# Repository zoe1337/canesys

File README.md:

# CANesys

Over CAN you said: let there be light (with 30% brightness).

And it was light (with 30% duty cycle).

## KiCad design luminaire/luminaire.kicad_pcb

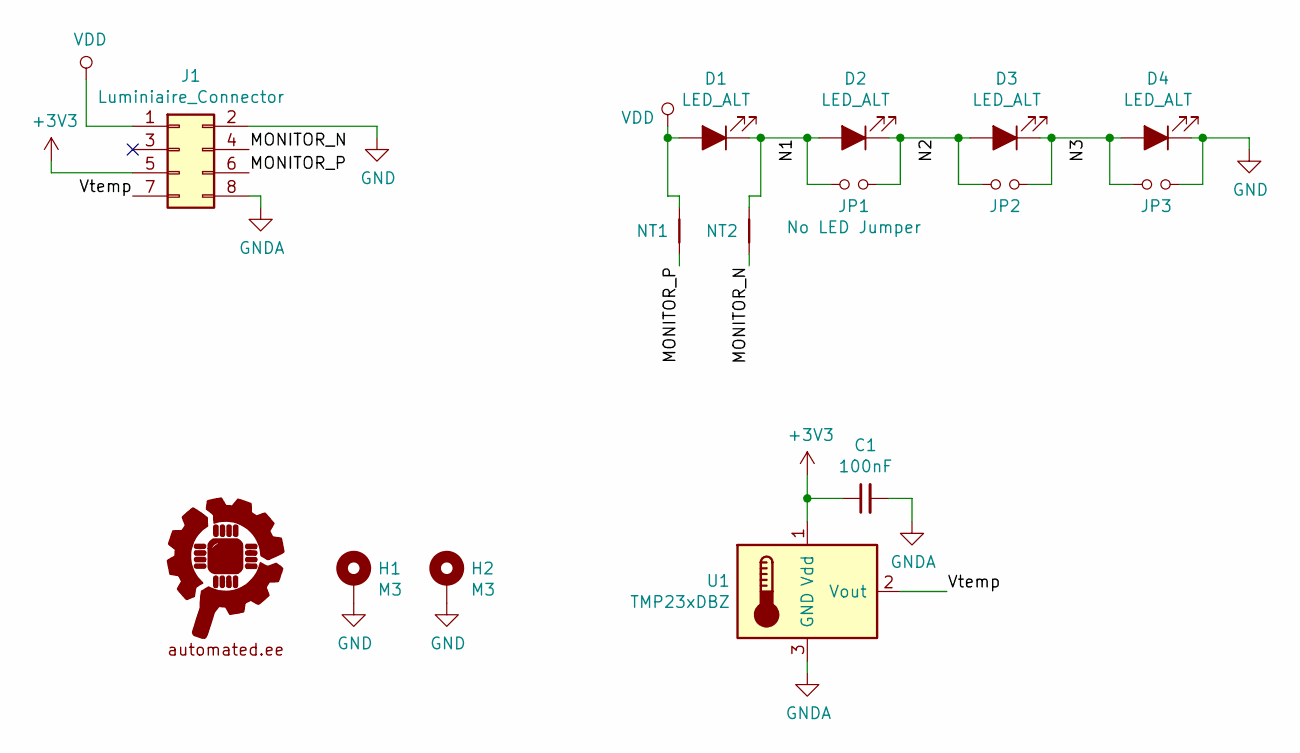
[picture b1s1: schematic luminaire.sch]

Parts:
C1: 100nF; C_0603_1608Metric
D1, D2, D3, D4: LED_ALT; LED_Osram_DURIS_S5_3x2.55x0.6mm
G1: Fully_Automated_Logo; falogo_small_copper
H1, H2: M3; MountingHole_3.2mm_M3_Pad_Via
J1: Luminiaire_Connector; PinHeader_2x04_P2.54mm_Vertical_SMD
JP1, JP2, JP3: No LED Jumper; SolderJumper-2_P1.3mm_Open_Pad1.0x1.5mm
NT1: MONITOR_P; NetTie-2_SMD_Pad0.5mm
NT2: NONITOR_N; NetTie-2_SMD_Pad0.5mm
U1: TMP23xDBZ; SOT-23

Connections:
+3V3: C1.1, J1.5, U1.1 (Vdd)
/MONITOR_N: J1.4, NT2.2
/MONITOR_P: J1.6, NT1.2
/N1: D1.1 (K), D2.2 (A), JP1.1, NT2.1
/N2: D2.1 (K), D3.2 (A), JP1.2, JP2.1
/N3: D3.1 (K), D4.2 (A), JP2.2, JP3.1
/Vtemp: J1.7, U1.2 (Vout)
GND: D4.1 (K), H1.1, H2.1, J1.2, JP3.2
GNDA: C1.2, J1.8, U1.3 (GND)
VDD: D1.2 (A), J1.1, NT1.1

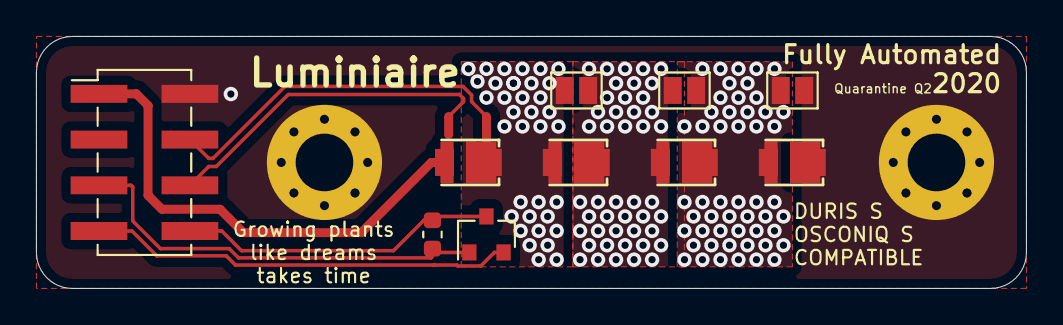
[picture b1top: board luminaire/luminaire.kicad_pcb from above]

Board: 2 copper layers, 55.0 x 14.0 mm, 15 parts (1 on the bottom side), 10 nets.

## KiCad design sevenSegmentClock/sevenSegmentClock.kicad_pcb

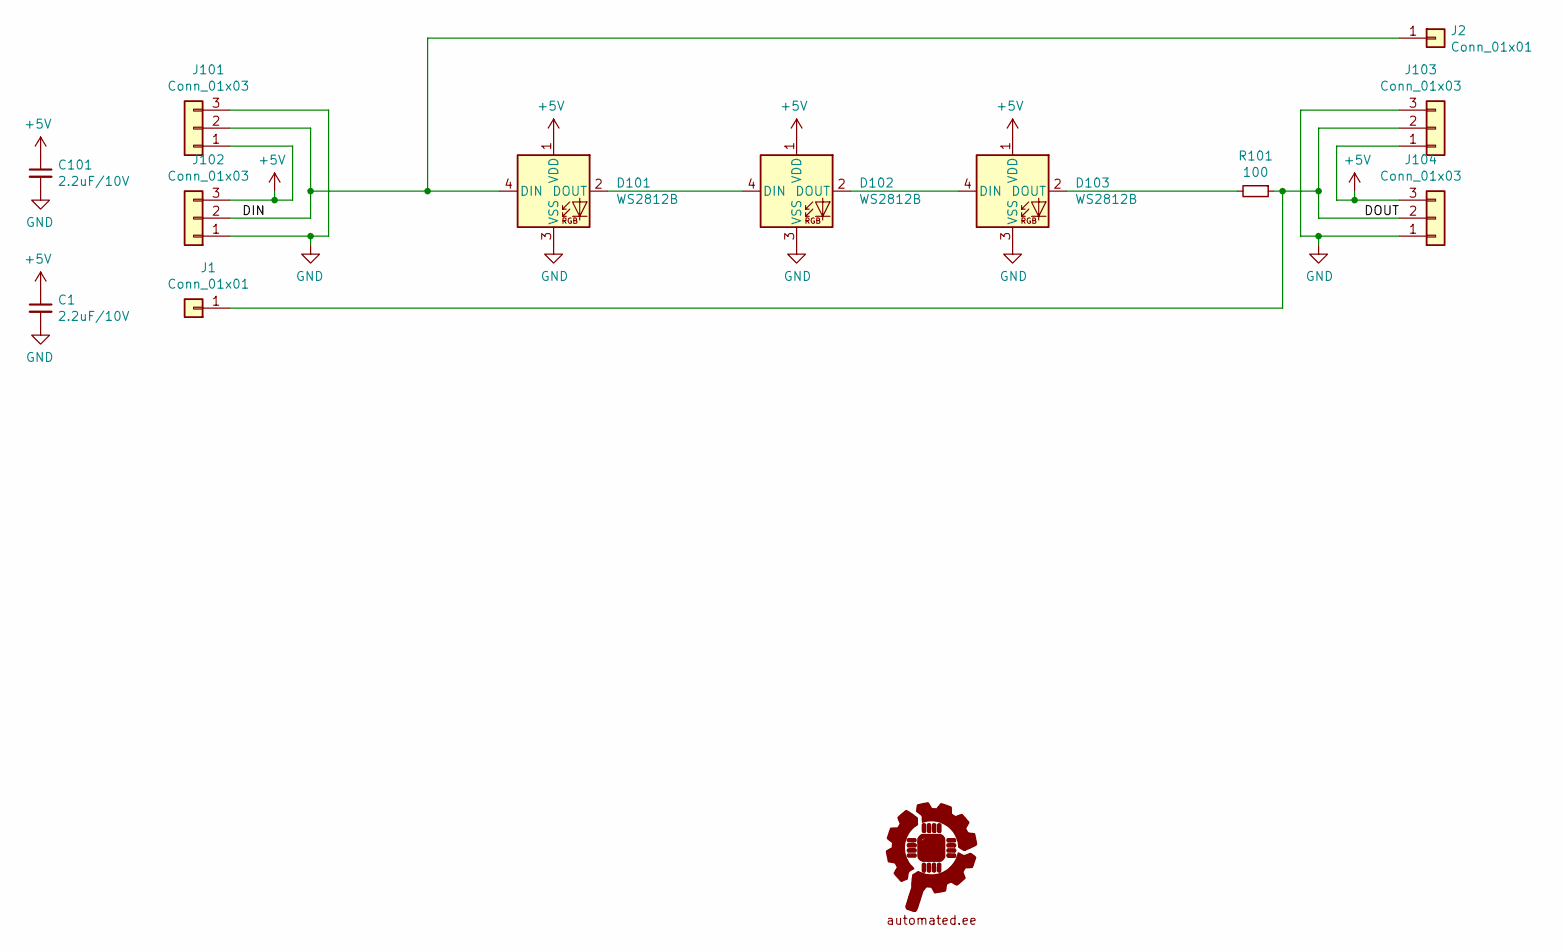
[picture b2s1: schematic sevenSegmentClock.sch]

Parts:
C1, C101: 2.2uF/10V; C_0603_1608Metric
D101, D102, D103: WS2812B; LED_SK6812MINI_PLCC4_3.5x3.5mm_P1.75mm
G101: Fully_Automated_Logo; fully_automated_logo_soldermask
J1, J2: Conn_01x01; TestPoint_THTPad_1.5x1.5mm_Drill0.7mm
J101, J102, J103, J104: Conn_01x03; PinHeader_1x03_P2.00mm_Vertical
R101: 100; R_0603_1608Metric

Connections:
+5V: C1.1, C101.1, D101.1 (VDD), D102.1 (VDD), D103.1 (VDD), J101.1, J102.3, J103.1, J104.3
/DIN: D101.4 (DIN), J2.1, J101.2, J102.2
/DOUT: J1.1, J103.2, J104.2, R101.1
GND: C1.2, C101.2, D101.3 (VSS), D102.3 (VSS), D103.3 (VSS), J101.3, J102.1, J103.3, J104.1
unnamed: D101.2 (DOUT), D102.4 (DIN)
unnamed: D102.2 (DOUT), D103.4 (DIN)
unnamed: D103.2 (DOUT), R101.2

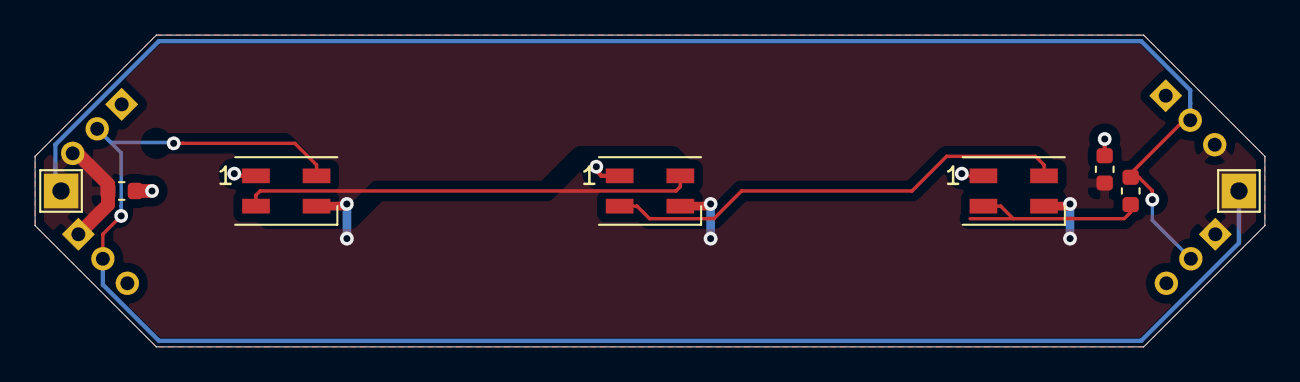
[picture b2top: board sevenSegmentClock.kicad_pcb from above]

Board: 2 copper layers, 71.0 x 18.0 mm, 13 parts (1 on the bottom side), 7 nets.

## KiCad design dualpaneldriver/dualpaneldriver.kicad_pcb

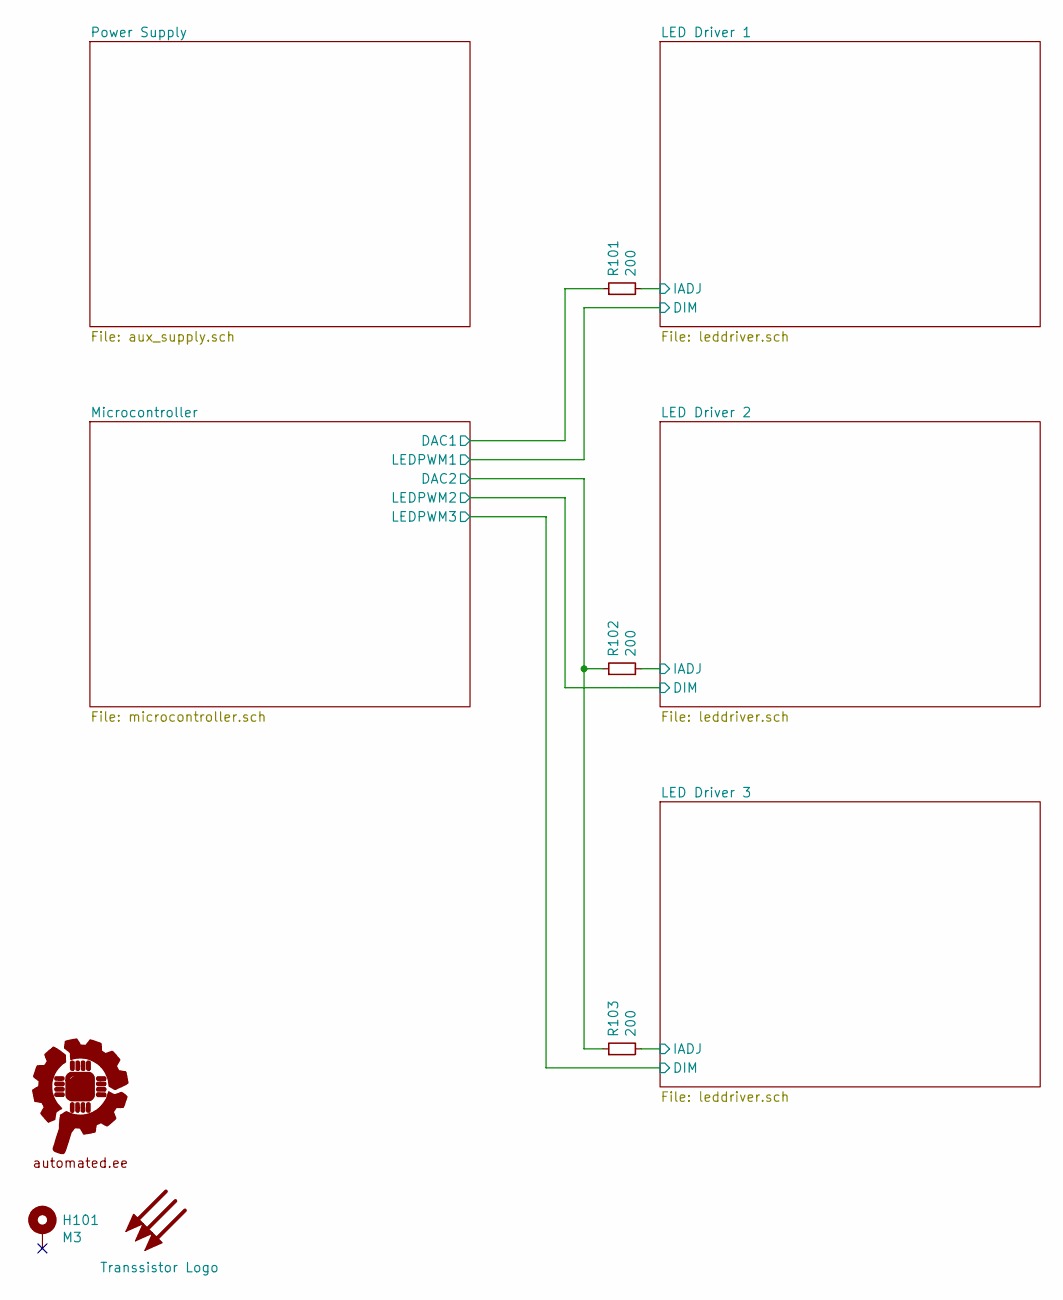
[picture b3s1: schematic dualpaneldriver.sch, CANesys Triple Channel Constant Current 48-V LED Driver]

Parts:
G101: Fully_Automated_Logo; falogo_small_copper
G102: Transsistor Logo; transistor_10x10mm
H101: M3; MountingHole_3.2mm_M3_ISO7380_Pad
R101, R102, R103: 200; R_0603_1608Metric

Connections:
/LED Driver 1/IADJ: R101.2; also elsewhere on the board
/LED Driver 2/IADJ: R102.2; also elsewhere on the board
/LED Driver 3/IADJ: R103.2; also elsewhere on the board
/Microcontroller/DAC1: R101.1; also elsewhere on the board
/Microcontroller/DAC2: R102.1, R103.1; also elsewhere on the board

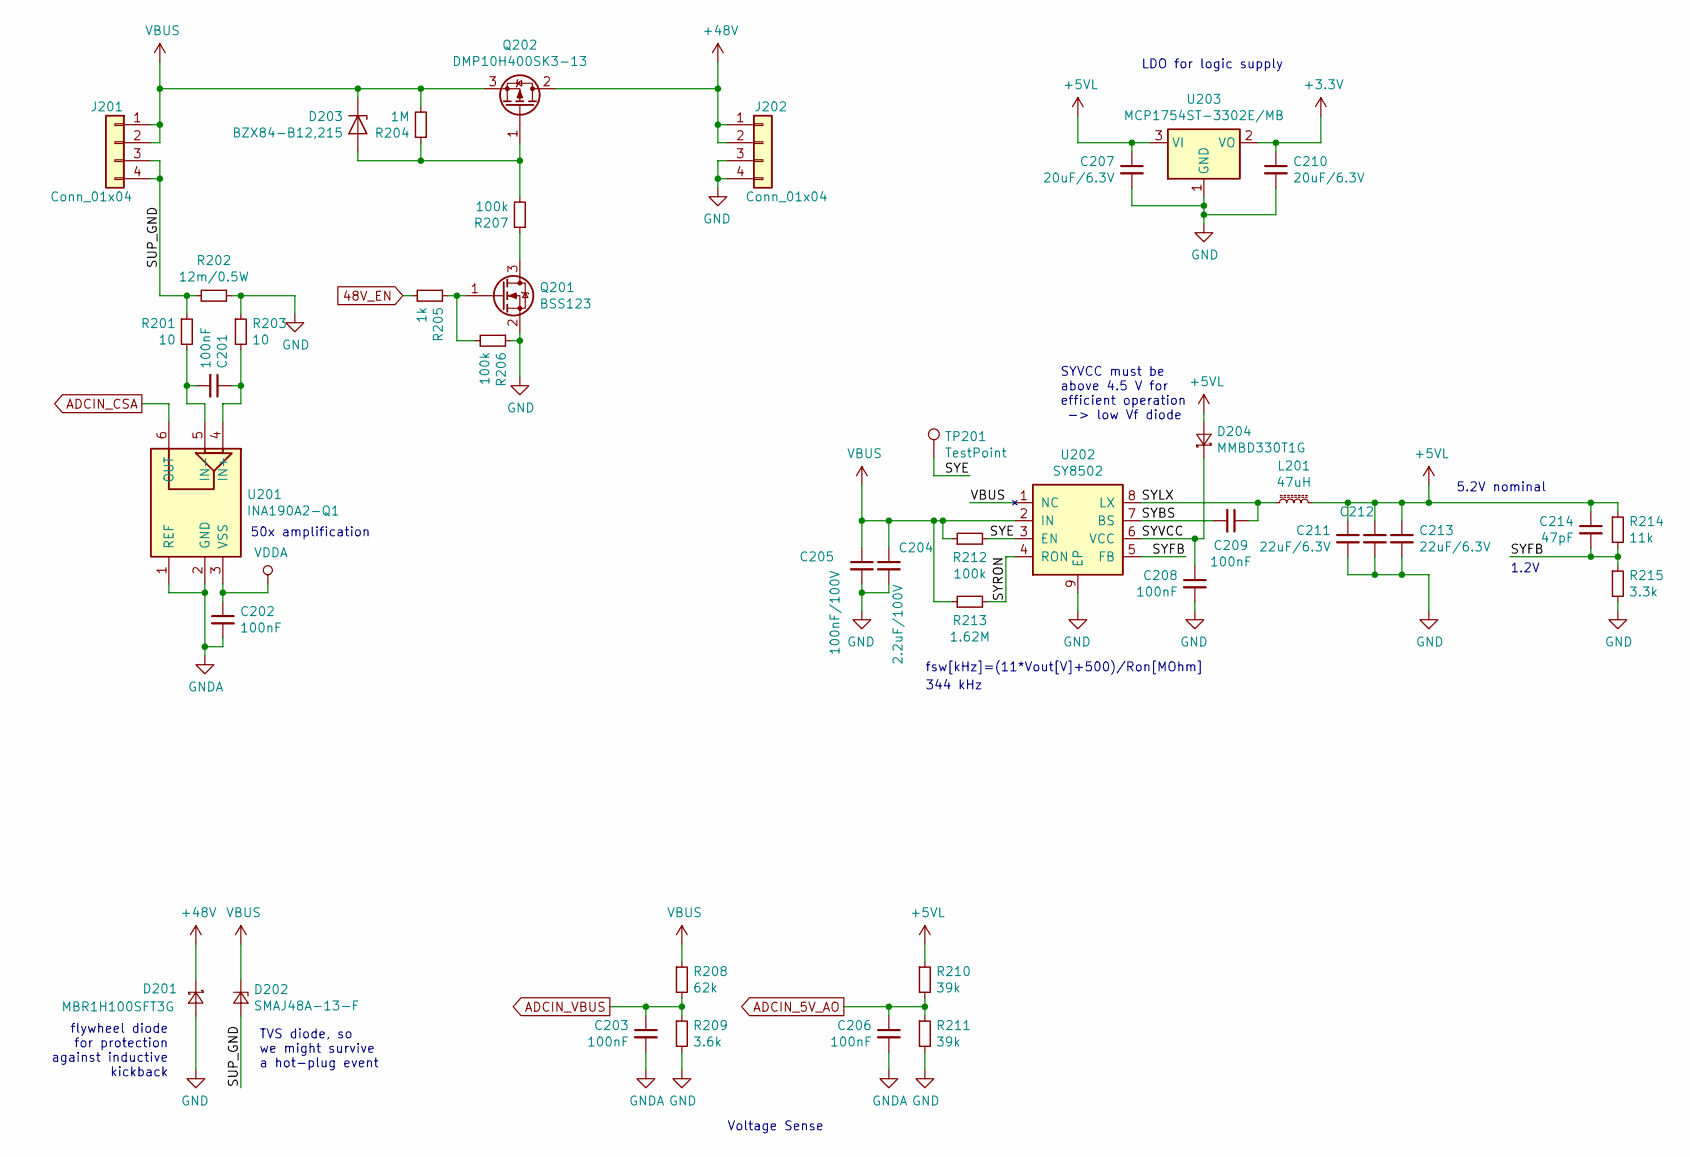
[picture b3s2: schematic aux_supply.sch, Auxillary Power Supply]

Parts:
C201, C202, C203, C206, C208: 100nF; C_0603_1608Metric
C204: 100nF/100V; C_0603_1608Metric
C205: 2.2uF/100V; C_1210_3225Metric
C207, C210: 20uF/6.3V; C_0805_2012Metric
C209: 100nF; C_0402_1005Metric
C211, C212, C213: 22uF/6.3V; C_0603_1608Metric
C214: 47pF; C_0603_1608Metric
D201: MBR1H100SFT3G; D_SOD-123F
D202: SMAJ48A-13-F; D_SMA
D203: BZX84-B12,215; D_SOT-23_ANK
D204: MMBD330T1G; D_SOT-23_ANK
J201, J202: Conn_01x04; PinHeader_1x04_P2.54mm_Horizontal
L201: 47uH; L_Bourns_SRN6045TA
Q201: BSS123; SOT-23
Q202: DMP10H400SK3-13; TO-252-2
R201, R203: 10; R_0603_1608Metric
R202: 12m/0.5W; R_2512_6332Metric
R204: 1M; R_0603_1608Metric
R205: 1k; R_0603_1608Metric
R206, R207, R212: 100k; R_0603_1608Metric
R208: 62k; R_0603_1608Metric
R209: 3.6k; R_0603_1608Metric
R210, R211: 39k; R_0603_1608Metric
R213: 1.62M; R_0603_1608Metric
R214: 11k; R_0603_1608Metric
R215: 3.3k; R_0603_1608Metric
TP201: TestPoint; TestPoint_Pad_1.0x1.0mm
U201: INA190A2-Q1; SOT-363_SC-70-6
U202: SY8502; SO8E_Silergy_4x5mm_EP3.4x2.55mm
U203: MCP1754ST-3302E/MB; SOT-89-3

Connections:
48V_EN: R205.2; also elsewhere on the board
+3V3: C210.1, U203.2 (VO); also elsewhere on the board
+5VL: C207.1, C211.1, C212.1, C213.1, C214.1, D204.2 (A), L201.2, R210.1, R214.1, U203.3 (VI); also elsewhere on the board
+48V: D201.1 (K), J202.1, J202.2, Q202.2 (D); also elsewhere on the board
/Power Supply/SUP_GND: D202.2 (A), J201.3, J201.4, R201.1, R202.2
/Power Supply/SYBS: C209.2, U202.7 (BS)
/Power Supply/SYE: R212.2, TP201.1, U202.3 (EN)
/Power Supply/SYFB: C214.2, R214.2, R215.1, U202.5 (FB)
/Power Supply/SYLX: C209.1, L201.1, U202.8 (LX)
/Power Supply/SYRON: R213.2, U202.4 (RON)
/Power Supply/SYVCC: C208.1, D204.1 (K), U202.6 (VCC)
ADCIN_5V_AO: C206.1, R210.2, R211.1; also elsewhere on the board
ADCIN_CSA: U201.6 (OUT); also elsewhere on the board
ADCIN_VBUS: C203.1, R208.2, R209.1; also elsewhere on the board
GND: C204.2, C205.2, C207.2, C208.2, C210.2, C211.2, C212.2, C213.2, D201.2 (A), J202.3, J202.4, Q201.2 (S), R202.1, R203.1, R206.1, R209.2, R211.2, R215.2, U202.9 (EP), U203.1 (GND); also elsewhere on the board
GNDA: C202.2, C203.2, C206.2, U201.1 (REF), U201.2 (GND); also elsewhere on the board
unnamed: C201.1, R203.2, U201.4 (IN+)
unnamed: C201.2, R201.2, U201.5 (IN-)
unnamed: D203.2 (A), Q202.1 (G), R204.1, R207.2
unnamed: Q201.1 (G), R205.1, R206.2
unnamed: Q201.3 (D), R207.1
VBUS: C204.1, C205.1, D202.1 (K), D203.1 (K), J201.1, J201.2, Q202.3 (S), R204.2, R208.1, R212.1, R213.1, U202.1 (NC), U202.2 (IN)
VDDA: C202.1, U201.3 (VSS); also elsewhere on the board

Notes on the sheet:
50x amplification
TVS diode, so we might survive a hot-plug event
5.2V nominal
344 kHz
fsw[kHz]=(11*Vout[V]+500)/Ron[MOhm]
1.2V
SYVCC must be above 4.5 V for efficient operation -> low Vf diode
flywheel diode for protection against inductive kickback
LDO for logic supply
Voltage Sense

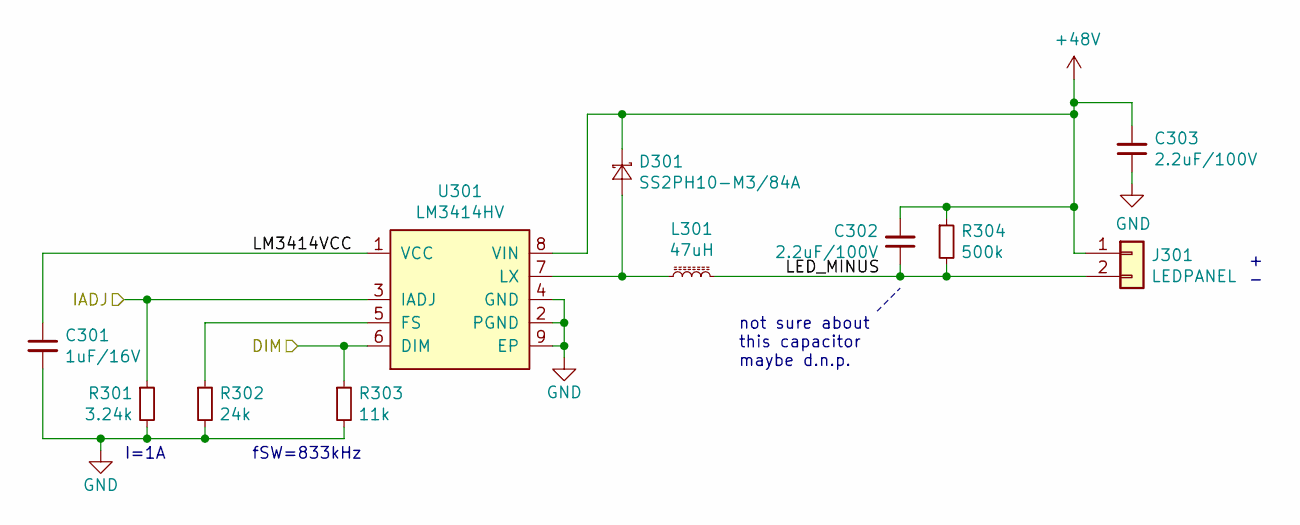
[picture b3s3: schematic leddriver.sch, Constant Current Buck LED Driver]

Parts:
C301: 1uF/16V; C_0603_1608Metric
C302, C303: 2.2uF/100V; C_1206_3216Metric
D301: SS2PH10-M3/84A; D_SMP_DO-220AA
J301: LEDPANEL; PinHeader_1x02_P2.54mm_Vertical
L301: 47uH; L_Bourns_SRN6045TA
R301: 3.24k; R_0603_1608Metric
R302: 24k; R_0603_1608Metric
R303: 11k; R_0603_1608Metric
R304: 500k; R_0603_1608Metric
U301: LM3414HV; SOIC-8-1EP_3.9x4.9mm_P1.27mm_EP2.29x3mm

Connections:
+48V: C302.2, C303.2, D301.1 (K), J301.1, R304.1, U301.8 (VIN); also elsewhere on the board
/LED Driver 1/DIM: R303.1, U301.6 (DIM); also elsewhere on the board
/LED Driver 1/IADJ: R301.1, U301.3 (IADJ); also elsewhere on the board
/LED Driver 1/LED_MINUS: C302.1, J301.2, L301.2, R304.2
/LED Driver 1/LM3414VCC: C301.1, U301.1 (VCC)
GND: C301.2, C303.1, R301.2, R302.2, R303.2, U301.2 (PGND), U301.4 (GND), U301.9 (EP); also elsewhere on the board
unnamed: D301.2 (A), L301.1, U301.7 (LX)
unnamed: R302.1, U301.5 (FS)

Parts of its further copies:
C501, C601: 1uF/16V; C_0603_1608Metric
C502, C503, C602, C603: 2.2uF/100V; C_1206_3216Metric
D501, D601: SS2PH10-M3/84A; D_SMP_DO-220AA
J501, J601: LEDPANEL; PinHeader_1x02_P2.54mm_Vertical
L501, L601: 47uH; L_Bourns_SRN6045TA
R501, R601: 3.24k; R_0603_1608Metric
R502, R602: 24k; R_0603_1608Metric
R503, R603: 11k; R_0603_1608Metric
R504, R604: 500k; R_0603_1608Metric
U501, U601: LM3414HV; SOIC-8-1EP_3.9x4.9mm_P1.27mm_EP2.29x3mm

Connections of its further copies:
+48V: C502.2, C503.2, C602.2, C603.2, D501.1 (K), D601.1 (K), J501.1, J601.1, R504.1, R604.1, U501.8 (VIN), U601.8 (VIN); also elsewhere on the board
/LED Driver 2/DIM: R503.1, U501.6 (DIM); also elsewhere on the board
/LED Driver 2/IADJ: R501.1, U501.3 (IADJ); also elsewhere on the board
/LED Driver 2/LED_MINUS: C502.1, J501.2, L501.2, R504.2
/LED Driver 2/LM3414VCC: C501.1, U501.1 (VCC)
/LED Driver 3/DIM: R603.1, U601.6 (DIM); also elsewhere on the board
/LED Driver 3/IADJ: R601.1, U601.3 (IADJ); also elsewhere on the board
/LED Driver 3/LED_MINUS: C602.1, J601.2, L601.2, R604.2
/LED Driver 3/LM3414VCC: C601.1, U601.1 (VCC)
GND: C501.2, C503.1, C601.2, C603.1, R501.2, R502.2, R503.2, R601.2, R602.2, R603.2, U501.2 (PGND), U501.4 (GND), U501.9 (EP), U601.2 (PGND), U601.4 (GND), U601.9 (EP); also elsewhere on the board
unnamed: D501.2 (A), L501.1, U501.7 (LX)
unnamed: D601.2 (A), L601.1, U601.7 (LX)
unnamed: R502.1, U501.5 (FS)
unnamed: R602.1, U601.5 (FS)

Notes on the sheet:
fSW=833kHz
I=1A
not sure about this capacitor maybe d.n.p.
+ -

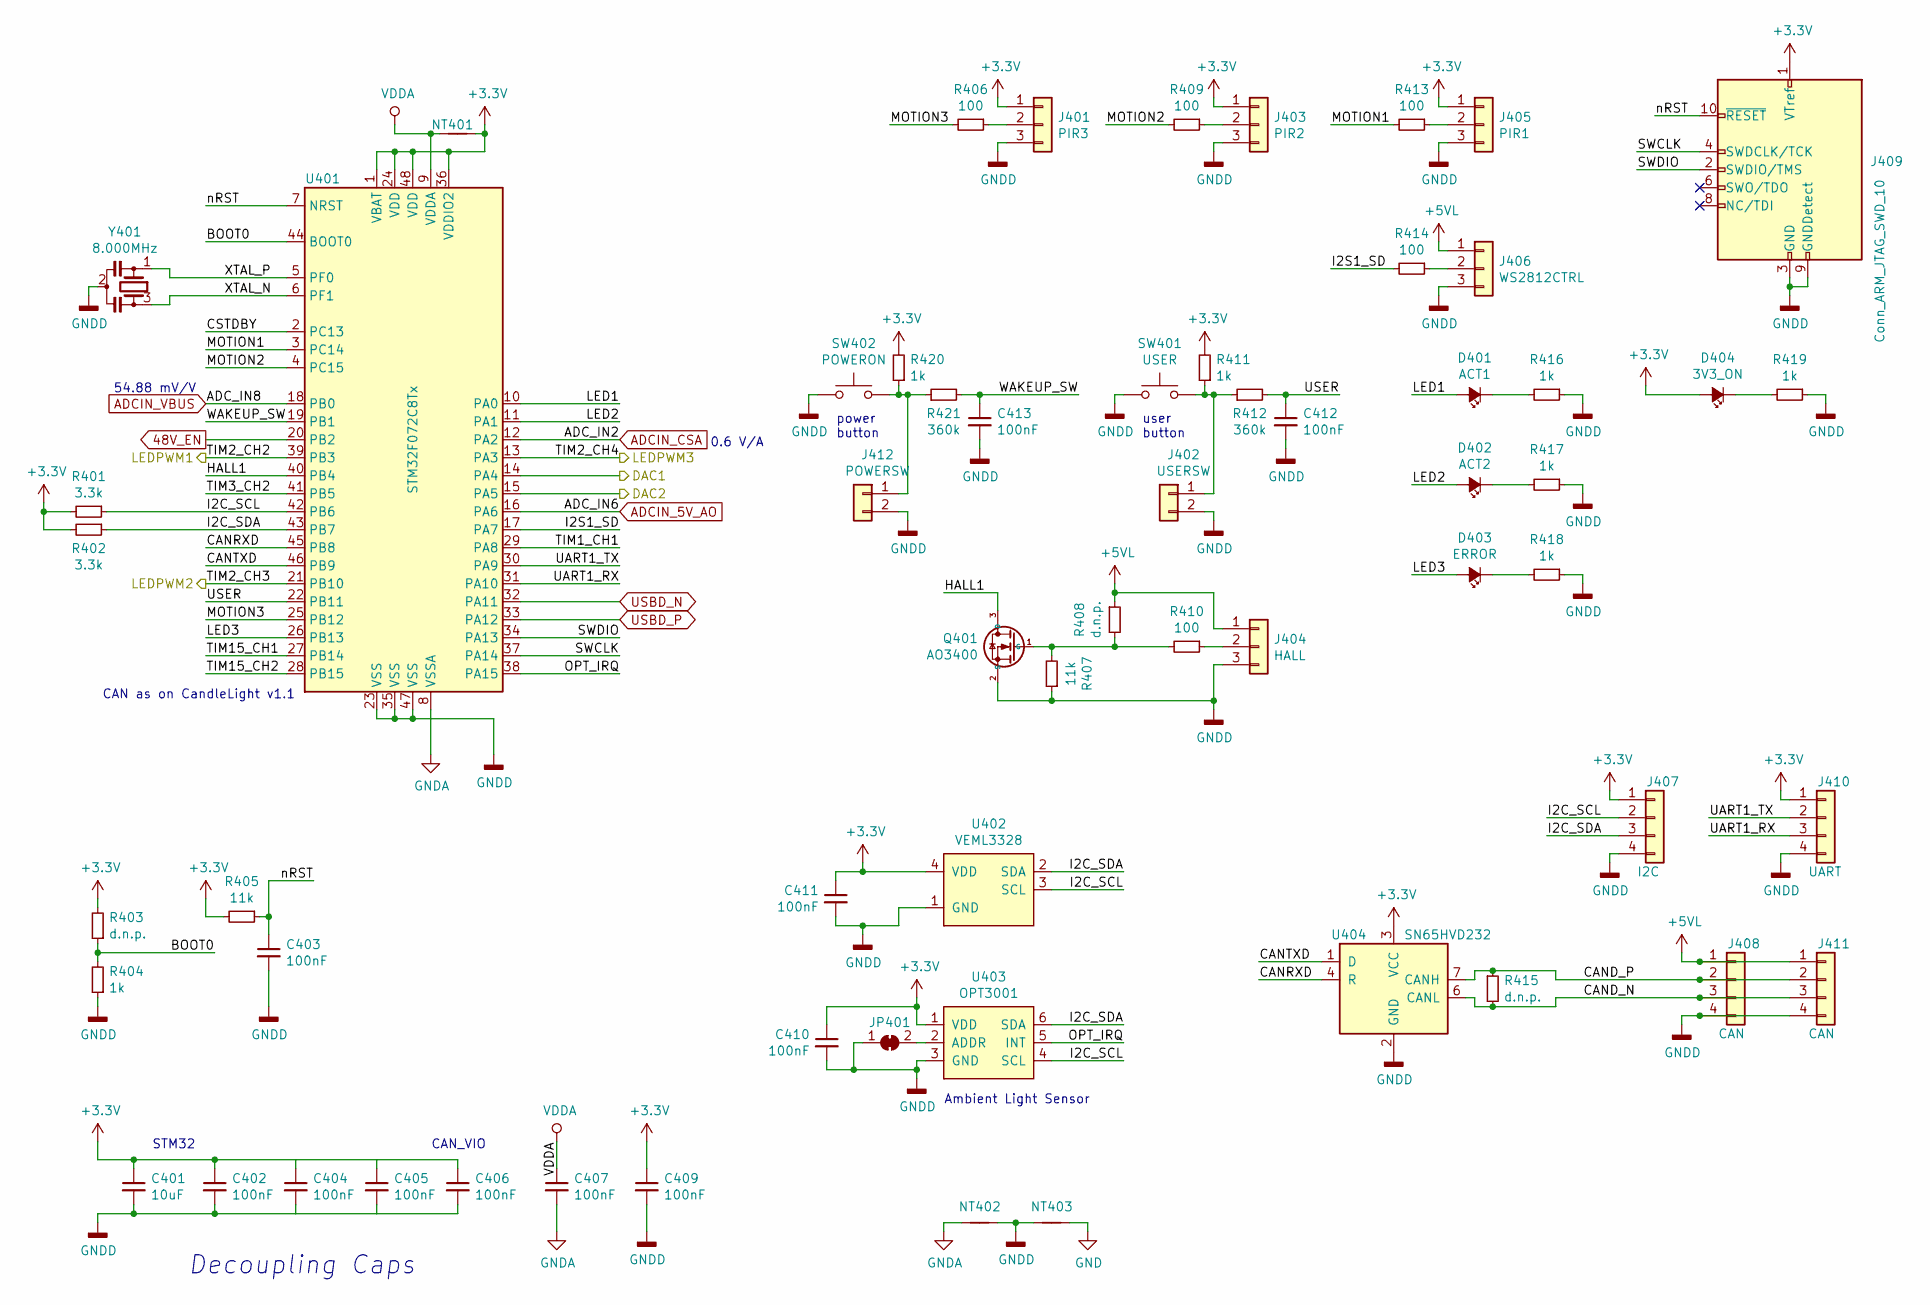
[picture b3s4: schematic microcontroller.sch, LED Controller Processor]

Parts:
C401: 10uF; C_0805_2012Metric
C402, C403, C404, C405, C406, C407, C409, C410, C411, C412, C413: 100nF; C_0603_1608Metric
D401: ACT1; LED_0603_1608Metric
D402: ACT2; LED_0603_1608Metric
D403: ERROR; LED_0603_1608Metric
D404: 3V3_ON; LED_0603_1608Metric
J401: PIR3; PinHeader_1x03_P2.54mm_Vertical
J402: USERSW; PinHeader_1x02_P2.54mm_Vertical
J403: PIR2; PinHeader_1x03_P2.54mm_Vertical
J404: HALL; PinHeader_1x03_P2.54mm_Vertical
J405: PIR1; PinHeader_1x03_P2.54mm_Vertical
J406: WS2812CTRL; PinHeader_1x03_P2.54mm_Vertical
J407: I2C; PinHeader_1x04_P2.54mm_Vertical
J408, J411: CAN; PinHeader_1x04_P2.54mm_Vertical
J409: Conn_ARM_JTAG_SWD_10; PinHeader_2x05_P1.27mm_Vertical_SMD
J410: UART; PinHeader_1x04_P2.54mm_Vertical
J412: POWERSW; PinHeader_1x02_P2.54mm_Vertical
JP401: SolderJumper_2_Bridged; SolderJumper-2_P1.3mm_Bridged_RoundedPad1.0x1.5mm
NT401, NT402, NT403: Net-Tie_2; NetTie-2_SMD_Pad0.5mm
Q401: AO3400; SOT-23
R401, R402: 3.3k; R_0603_1608Metric
R403, R408, R415: d.n.p.; R_0603_1608Metric
R404, R411, R416, R417, R418, R419, R420: 1k; R_0603_1608Metric
R405, R407: 11k; R_0603_1608Metric
R406, R409, R410, R413, R414: 100; R_0603_1608Metric
R412, R421: 360k; R_0603_1608Metric
SW401: USER; SW_SPST_PTS636_G
SW402: POWERON; SW_SPST_PTS636_G
U401: STM32F072C8Tx; LQFP-48_7x7mm_P0.5mm
U402: VEML3328; Vishay_LGA-4_VEML_2x1.25mm
U403: OPT3001; TI_USON-6_DNP0006A_2x2mm_EP_1.35x0.65mm_P0.65mm
U404: SN65HVD232; SOIC-8_3.9x4.9mm_P1.27mm
Y401: 8.000MHz; Resonator_SMD_muRata_CSTxExxV-3Pin_3.0x1.1mm

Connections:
48V_EN: U401.20 (PB2); also elsewhere on the board
+3V3: C401.1, C402.1, C404.1, C405.1, C406.1, C409.1, C410.1, C411.1, D404.2 (A), J401.1, J403.1, J405.1, J407.1, J409.1 (VTref), J410.1, NT401.1, R401.2, R402.2, R403.2, R405.2, R411.2, R420.2, U401.1 (VBAT), U401.24 (VDD), U401.36 (VDDIO2), U401.48 (VDD), U402.4 (VDD), U403.1 (VDD), U404.3 (VCC); also elsewhere on the board
+5VL: J404.1, J406.1, J408.1, J411.1, R408.1; also elsewhere on the board
/LED Driver 1/DIM: U401.39 (PB3); also elsewhere on the board
/LED Driver 2/DIM: U401.21 (PB10); also elsewhere on the board
/LED Driver 3/DIM: U401.13 (PA3); also elsewhere on the board
/Microcontroller/BOOT0: R403.1, R404.2, U401.44 (BOOT0)
/Microcontroller/CAND_N: J408.3, J411.3, R415.2, U404.6 (CANL)
/Microcontroller/CAND_P: J408.2, J411.2, R415.1, U404.7 (CANH)
/Microcontroller/CANRXD: U401.45 (PB8), U404.4 (R)
/Microcontroller/CANTXD: U401.46 (PB9), U404.1 (D)
/Microcontroller/CSTDBY: U401.2 (PC13)
/Microcontroller/DAC1: U401.14 (PA4); also elsewhere on the board
/Microcontroller/DAC2: U401.15 (PA5); also elsewhere on the board
/Microcontroller/HALL1: Q401.3 (D), U401.40 (PB4)
/Microcontroller/I2C_SCL: J407.2, R401.1, U401.42 (PB6), U402.3 (SCL), U403.4 (SCL)
/Microcontroller/I2C_SDA: J407.3, R402.1, U401.43 (PB7), U402.2 (SDA), U403.6 (SDA)
/Microcontroller/I2S1_SD: R414.2, U401.17 (PA7)
/Microcontroller/LED1: D401.2 (A), U401.10 (PA0)
/Microcontroller/LED2: D402.2 (A), U401.11 (PA1)
/Microcontroller/LED3: D403.2 (A), U401.26 (PB13)
/Microcontroller/MOTION1: R413.2, U401.3 (PC14)
/Microcontroller/MOTION2: R409.2, U401.4 (PC15)
/Microcontroller/MOTION3: R406.2, U401.25 (PB12)
/Microcontroller/OPT_IRQ: U401.38 (PA15), U403.5 (INT)
/Microcontroller/SWCLK: J409.4 (SWDCLK/TCK), U401.37 (PA14)
/Microcontroller/SWDIO: J409.2 (SWDIO/TMS), U401.34 (PA13)
/Microcontroller/TIM1_CH1: U401.29 (PA8)
/Microcontroller/TIM3_CH2: U401.41 (PB5)
/Microcontroller/TIM15_CH1: U401.27 (PB14)
/Microcontroller/TIM15_CH2: U401.28 (PB15)
/Microcontroller/UART1_RX: J410.3, U401.31 (PA10)
/Microcontroller/UART1_TX: J410.2, U401.30 (PA9)
/Microcontroller/USER: C412.1, R412.2, U401.22 (PB11)
/Microcontroller/WAKEUP_SW: C413.1, R421.2, U401.19 (PB1)
/Microcontroller/XTAL_N: U401.6 (PF1), Y401.3
/Microcontroller/XTAL_P: U401.5 (PF0), Y401.1
/Microcontroller/nRST: C403.1, J409.10 (~RESET~), R405.1, U401.7 (NRST)
ADCIN_5V_AO: U401.16 (PA6); also elsewhere on the board
ADCIN_CSA: U401.12 (PA2); also elsewhere on the board
ADCIN_VBUS: U401.18 (PB0); also elsewhere on the board
GND: NT403.2; also elsewhere on the board
GNDA: C407.2, NT402.1, U401.8 (VSSA); also elsewhere on the board
GNDD: C401.2, C402.2, C403.2, C404.2, C405.2, C406.2, C409.2, C410.2, C411.2, C412.2, C413.2, J401.3, J402.2, J403.3, J404.3, J405.3, J406.3, J407.4, J408.4, J409.3 (GND), J409.5 (GND), J409.9 (GNDDetect), J410.4, J411.4, J412.2, JP401.1 (A), NT402.2, NT403.1, Q401.2 (S), R404.1, R407.1, R416.1, R417.1, R418.1, R419.1, SW401.1, SW402.1, U401.23 (VSS), U401.35 (VSS), U401.47 (VSS), U402.1 (GND), U403.3 (GND), U404.2 (GND), Y401.2
unnamed: D401.1 (K), R416.2
unnamed: D402.1 (K), R417.2
unnamed: D403.1 (K), R418.2
unnamed: D404.1 (K), R419.2
unnamed: J401.2, R406.1
unnamed: J402.1, R411.1, R412.1, SW401.2
unnamed: J403.2, R409.1
unnamed: J404.2, R410.1
unnamed: J405.2, R413.1
unnamed: J406.2, R414.1
unnamed: J412.1, R420.1, R421.1, SW402.2
unnamed: JP401.2 (B), U403.2 (ADDR)
unnamed: Q401.1 (G), R407.2, R408.2, R410.2
USBD_N: U401.32 (PA11)
USBD_P: U401.33 (PA12)
VDDA: C407.1, NT401.2, U401.9 (VDDA); also elsewhere on the board

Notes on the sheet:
STM32
Decoupling Caps
CAN_VIO
54.88 mV/V
power button
CAN as on CandleLight v1.1
0.6 V/A
Ambient Light Sensor
user button

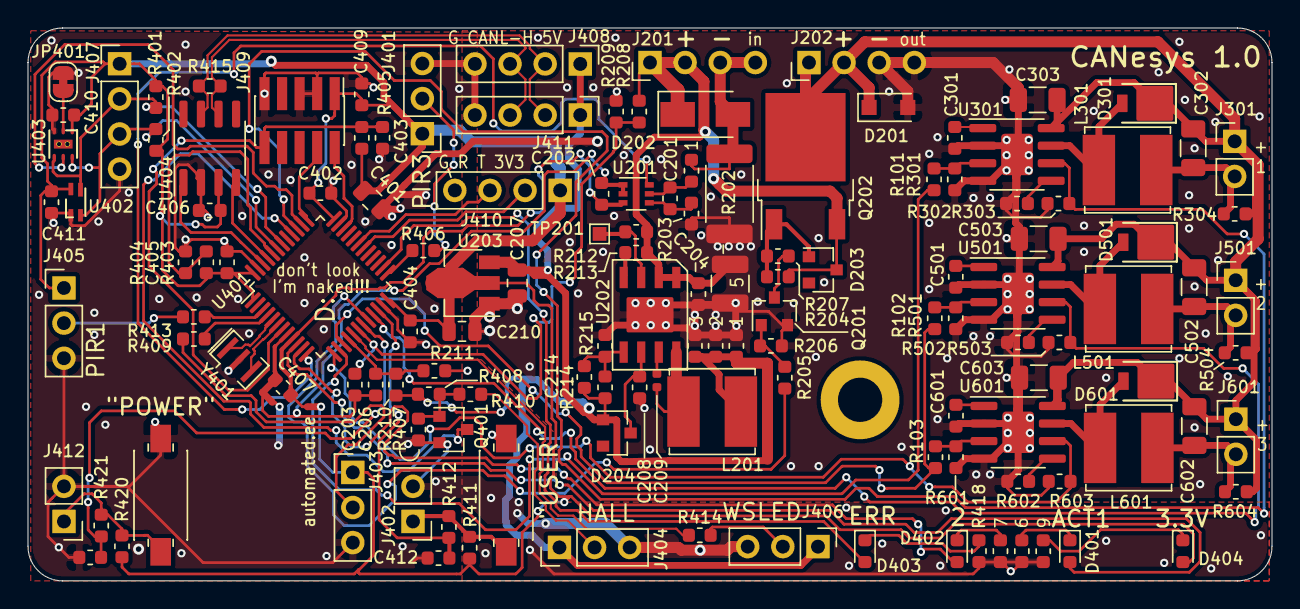
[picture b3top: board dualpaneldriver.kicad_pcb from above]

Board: 2 copper layers, 90.0 x 40.0 mm, 142 parts (1 on the bottom side), 82 nets.

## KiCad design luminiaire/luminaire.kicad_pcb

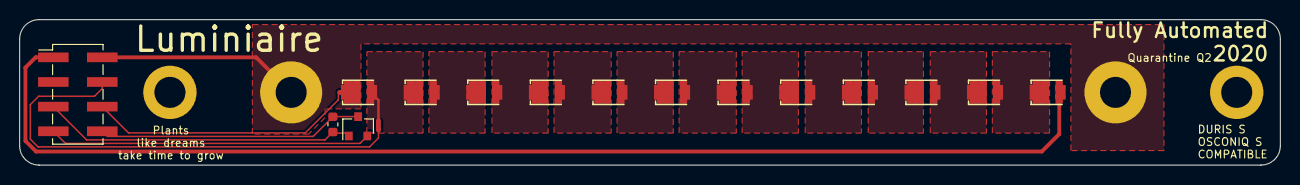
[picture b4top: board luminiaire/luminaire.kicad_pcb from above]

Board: 2 copper layers, 130.0 x 15.0 mm, 22 parts (1 on the bottom side), 18 nets.

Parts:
C1: 100nF; C_0603_1608Metric
D1, D2, D3, D4, D5, D6, D7, D8, D9, D10, D11, D12: LED_ALT; LED_Osram_DURIS_S5_3x2.55x0.6mm
G1: Fully_Automated_Logo; falogo_small_copper
H1, H2: M3; MountingHole_3.2mm_M3_Pad
H3, H4: M3; MountingHole_3.2mm_M3_ISO14580_Pad
J1: Luminiaire_Connector; PinHeader_2x04_P2.54mm_Vertical_SMD
NT1: MONITOR_P; NetTie-2_SMD_Pad0.5mm
NT2: NONITOR_N; NetTie-2_SMD_Pad0.5mm
U1: TMP23xDBZ; SOT-23

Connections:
+3V3: C1.1, J1.5, U1.1
/MONITOR_N: J1.6, NT2.2
/MONITOR_P: J1.4, NT1.2
/N1: D11.1, D12.2, NT1.1
/N2: D10.1, D11.2
/N3: D9.1, D10.2
/N4: D8.1, D9.2
/N5: D7.1, D8.2
/N6: D6.1, D7.2
/N7: D5.1, D6.2
/N8: D4.1, D5.2
/N9: D3.1, D4.2
/N10: D2.1, D3.2
/N11: D1.1, D2.2
/Vtemp: J1.7, U1.2
GND: D12.1, H1.1, H2.1, J1.2, NT2.1
GNDA: C1.2, J1.8, U1.3
VDD: D1.2, J1.1

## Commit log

2019-11-27 schematic done, footprints are missing
2019-11-29 added Hall Op Amp
2019-11-29 removed op amp
2019-12-01 some components placed
2019-12-02 i'm too sleepy to continue
2019-12-02 100% routed, silkscreen still fucked up
2019-12-03 I think it is done!?!
2019-12-06 done!
2019-12-08 changed input cap on the LED driver's DCDC
2019-12-08 made the board chonky
2019-12-08 changed logo from silkscreen to solder mask
2019-12-09 added arrows and shit
2020-01-01 added schematic PDFs
2020-01-01 added PDFs and photo
2020-01-01 added giant 7-segment project
2020-01-02 resized images
2020-01-02 wrote tinypol/README.md
2020-01-02 changed DIS to OFF, to match silk
2020-01-02 fixed image URLs to work on github too
2020-01-02 oops a leading slash was missing
2020-01-03 added the render with explanations
2020-01-03 included render in readme
2020-01-03 removed unnecessary line breaks from markdown
2020-01-03 minor fixes
2020-04-04 Add luminiaire files
2020-04-05 Add luster LED driver
2020-08-11 forgot to add luminiaire...
2020-08-11 meep
2020-08-11 updated footprint with the one of the correct 3D model
2020-08-14 added printable jigs
